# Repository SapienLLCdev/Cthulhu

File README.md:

## Cthulhu_Shield_Arduino

This is a library for using the Cthulhu Shield sensory substitution/augmentation development kit created by [Sapien LLC](http://sapienllc.com/). 

If you like what you see here, you can purchase a Cthulhu Shield [here!](https://sapienllc.com/shop/)

The Cthulhu Shield is an open-source Arduino Uno and Arduino Mega compatible sensory substitution/sensory augmentation device. It uses an 18 electrode grid to tactiley display signals on the tongue. The electrodes on the array can be activated with patterns of electrical pulses to depolarize nerve membranes in the tongue to create different types of touch sensations. You can use these touch sensations to draw shapes or simple images on the tongue, feel different sound frequencies, or receive turn by turn directions with your tongue.

Additionally, the Cthulhu Shield can sense whether or not your tongue is in contact with different electrodes using capacitive sensing. You can use the Cthulhu Shield to send keystrokes to your computer, control the cursor, or even control a mobility device. 

In this repository, we have provided a number of example projects to get you started with your Cthulhu, but we encourage you to experiment and build your own senses!

There are some awesome uses of sensory substitution already out there. For more information on these uses, or sensory substitution or augmentation in general, take a look at the links below. 
* [Brainport](https://www.youtube.com/watch?v=OKd56D2mvN0)
* [Wikipedia](https://en.wikipedia.org/wiki/Sensory_substitution)
* [Hear with your tongue](https://source.colostate.edu/words-mouth-csu-device-lets-hear-tongue/)
* [TedTalk](https://www.ted.com/talks/david_eagleman_can_we_create_new_senses_for_humans?language=en)

# Repository Contents:

* [Bare Minimum](https://github.com/SapienLLCdev/Cthulhu/tree/master/examples/BareMinimum)
* [Serial Input](https://github.com/SapienLLCdev/Cthulhu/tree/master/examples/SerialInput)
* [Accelerometer Example](https://github.com/SapienLLCdev/Cthulhu/tree/master/examples/accelerometer_Cthulhu_example)
* [GPS Directions](https://github.com/SapienLLCdev/Cthulhu/tree/master/examples/directions_example)
* [Make Patterns](https://github.com/SapienLLCdev/Cthulhu/tree/master/examples/make_patterns)
* [Thermal Camera](https://github.com/SapienLLCdev/Cthulhu/tree/master/examples/mega_heat_cam_with_shield)
* [Tactile Button](https://github.com/SapienLLCdev/Cthulhu/tree/master/examples/tactile_button_example)
* [Tactile Cursor](https://github.com/SapienLLCdev/Cthulhu/tree/master/examples/tactile_cursor)
* [Leonardo Tactile Cursor](https://github.com/SapienLLCdev/Cthulhu/tree/master/examples/Leonardo_tactile_cursor)
* [Tactile Keypad](https://github.com/SapienLLCdev/Cthulhu/tree/master/examples/tactile_keypad)
* [Cthulhu Camera Demo](https://github.com/SapienLLCdev/Cthulhu/tree/master/Android%20Examples/CthulhuCameraDemo)

# Cthulhu Shield Schematic:

.

# How to Use the Cthulhu Shield:

**Power:**
The Cthulhu Shield is made to be powered by plugging it directly into an Arduino Uno or Mega, and connecting the arduino to a USB cable attached to a properly grounded computer, or a smartphone or external battery pack. Users should not power their Arduino/Cthulhu Shield system with an AC wall adaptor, as a small number of these adaptors are not properly grounded or are otherwise unsafe and can cause injury or death if used with any electronic device.

**Input:**
When used with an Arduino Uno, the Cthulhu Shield can receive information directly from the USB port connected to a computer or smartphone, or via broken out Serial pins (RX, TX) which can used to communicate with other Arduinos/microcontrollers, or embedded devices such as Bluetooth modules or sensors with serial outputs. With an Arduino Mega, the extra IO pins can be leveraged to receive Digital or Analog signals that can be used to change the tactile output of the Cthulhu Shield. 

**Output:**
When used with an Arduino Uno, the Cthulhu Shield can send information directly via USB port connected to a computer or smarptphone, or via broken out Serial pins (RX, TX) which can used to communicate with other Arduinos/microcontrollers, or embedded devices such as Bluetooth modules or sensors with serial outputs. With an Arduino Mega, the extra IO pins can be leveraged to send Digital or Analog signals to external devices. 

**Electrode Control:**
Different types of sensations can be created on different electrodes and tongue locations by changing the pattern of pulses generated on each electrode. This can be done with the Cthulhu.UpdateStimuli() function. A user changes values in six (6), eighteen (18) element arrays. The values in these arrays correspond to whether one of the 18 electrodes is on or off, and what type of pulse, and pattern of pulses, is created on each electrode. Changing these patterns changes the type and quality of the sensation perceived by the user. This library was adapted from [work by Kurt Kaczmarek](https://www.sciencedirect.com/science/article/pii/S1026309811001702) and altered for the needs of our early research at Sapien LLC.

**Tongue Position Sensing:**
During electrotactile stimulation with the Cthulhu Shield, the Arduino can quickly sense the electrical potential on a given electrode, which changes if the tongue is in contact with the electrode or not. Placing your tongue on certain electrodes but not others, or swiping your tongue across different electrodes, can be detected by the Arduino, which can then send serial information (or with minor hacking, keystrokes and HID signals) to a computer or smartphone via the USB port, or external Bluetooth modules. 

Currently, tongue-position-sensing is supported only on ADC enabled Arduino pins (A0-A5 on the Uno and Mega). Position sensing on digital only pins should be possible and may be implemented in the near future. 

# How to Use this Repository:

If you are new to Github, Sparkfun has created an [excellent Github tutorial](https://learn.sparkfun.com/tutorials/using-github/all). If you want to get up and running quickly, just take a look at the [Download ZIP](https://learn.sparkfun.com/tutorials/using-github/all#download-zip) section.

Similarly, if you are new to Arduino, Sparkfun once again has a great [guide to installing Arduino Libraries](https://learn.sparkfun.com/tutorials/installing-an-arduino-library). After downloading the .ZIP file of the library you want from Github, follow the instructions above to integrate it with the Arduino IDE.

Please see the README files in the examples linked above for more information on their specific implementations!

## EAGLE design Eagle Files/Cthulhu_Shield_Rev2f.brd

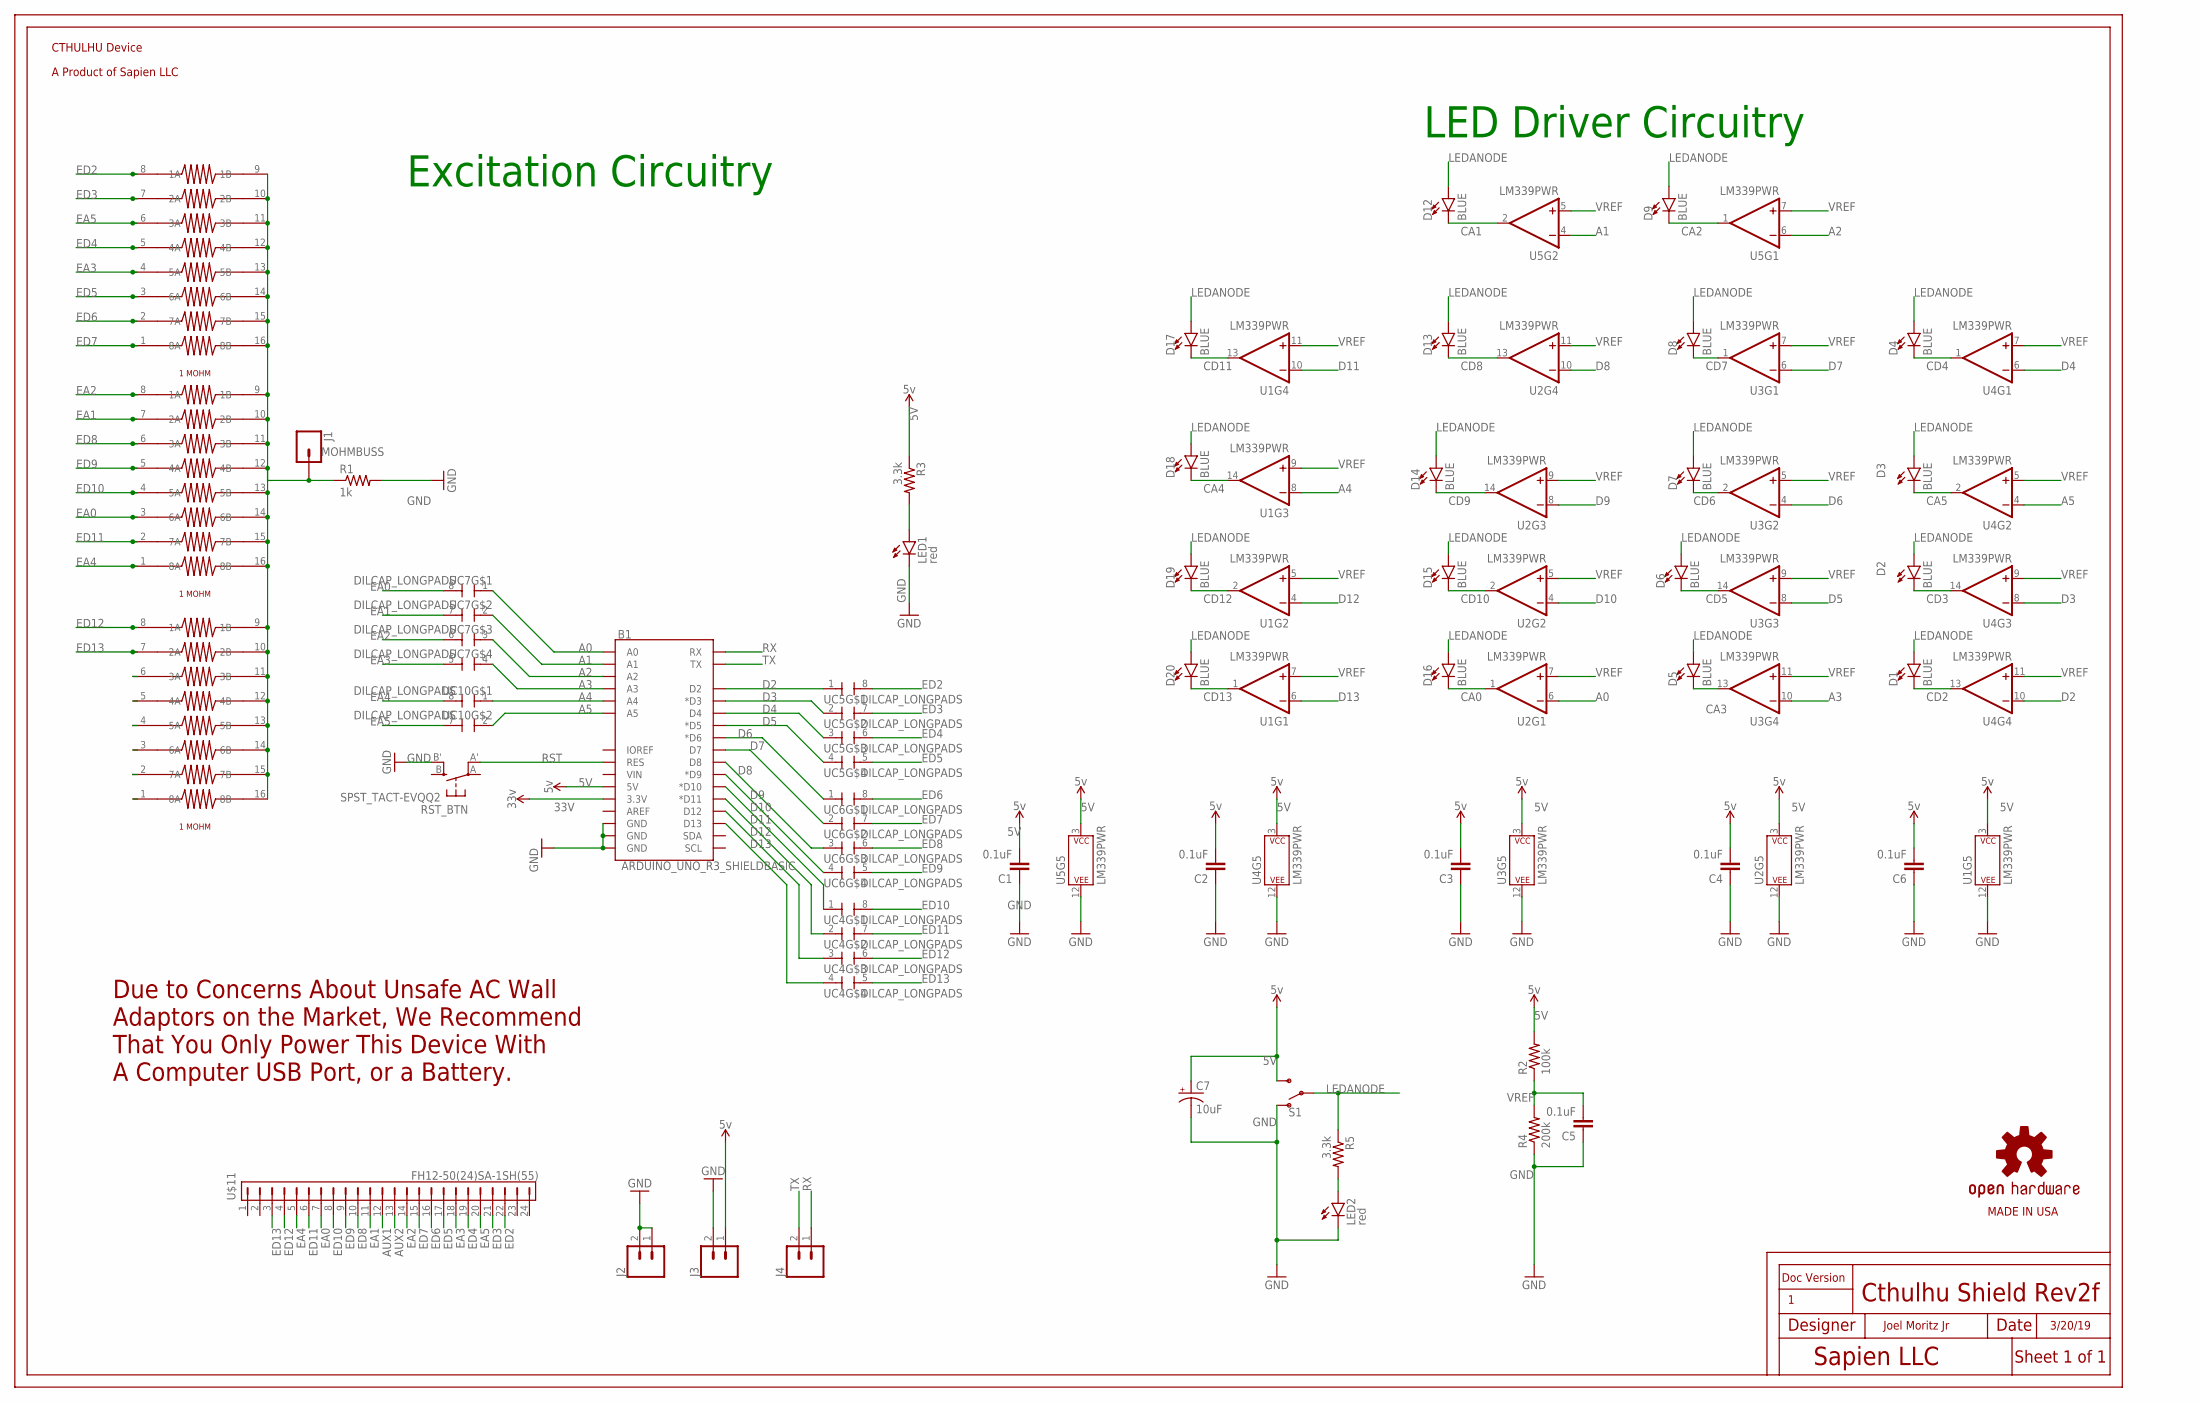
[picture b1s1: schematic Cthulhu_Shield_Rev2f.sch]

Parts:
B1: ARDUINO_UNO_R3_SHIELDBASIC; UNO_R3_SHIELD
C1, C2, C3, C4, C5, C6: 0.1uF; 0603
C7: 10uF; EIA3528
D1, D2, D3, D4, D5, D6, D7, D8, D9, D12, D13, D14, D15, D16, D17, D18, D19, D20: BLUE; LED-0603
J1: CONN_01; 1X01
J2, J3, J4: CONN_02; 1X02
LED1, LED2: red; LED-1206
LOGO1: OSHW-LOGOL; OSHW-LOGO-L
R1: 1k; 0402
R2: 100k; 0402
R3, R5: 3.3k; 0402
R4: 200k; 0402
RST_BTN: SPST_TACT-EVQQ2; EVQ-Q2
S1: SWITCH-SPDT-SMD-AYZ0202; SWITCH_DPDT_SMD_AYZ0202
U1, U2, U3, U4, U5: LM339PWR; TSSOP-14
U$1, U$2, U$3: 1MOHM8; JJ_CUSTOM_PARTS_1MOHMARRAY
U$4: NO_WALL_ADAPTOR
U$5: MADEINUSA
U$8: SAPEIN_LOGO_BOTTOM; SAPIEN_LOGO_BOTTOM
U$9: CTHULHU_LOGO; CTHULHU
U$11: FH12-50(24)SA-1SH(55); FH12-16S-1SH
UC4, UC5, UC6, UC7, UC10: DILCAP_LONGPADS; RESISTOR-DIL_4X0402ARV341_LONGPADS

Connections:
5V: B1.5V, C1.2, C2.2, C3.2, C4.2, C6.2, C7.A (+), J3.1, R2.2, R3.1, S1.3 (S), U1.3 (P$V+), U2.3 (P$V+), U3.3 (P$V+), U4.3 (P$V+), U5.3 (P$V+)
33V: B1.3.3V
A0: B1.A0, U2.6 (-IN), UC7.1
A1: B1.A1, U5.4 (-IN), UC7.2 (1)
A2: B1.A2, U5.6 (-IN), UC7.3 (1)
A3: B1.A3, U3.10 (-IN), UC7.4 (1)
A4: B1.A4, U1.8 (-IN), UC10.1
A5: B1.A5, U4.4 (-IN), UC10.2 (1)
AUX1: U$11.12
AUX2: U$11.13
CA0: D16.C, U2.1 (OUT)
CA1: D12.C, U5.2 (OUT)
CA2: D9.C, U5.1 (OUT)
CA3: D5.C, U3.13 (OUT)
CA4: D18.C, U1.14 (OUT)
CA5: D3.C, U4.2 (OUT)
CD2: D1.C, U4.13 (OUT)
CD3: D2.C, U4.14 (OUT)
CD4: D4.C, U4.1 (OUT)
CD5: D6.C, U3.14 (OUT)
CD6: D7.C, U3.2 (OUT)
CD7: D8.C, U3.1 (OUT)
CD8: D13.C, U2.13 (OUT)
CD9: D14.C, U2.14 (OUT)
CD10: D15.C, U2.2 (OUT)
CD11: D17.C, U1.13 (OUT)
CD12: D19.C, U1.2 (OUT)
CD13: D20.C, U1.1 (OUT)
D2: B1.D2, U4.10 (-IN), UC5.1
D3: B1.D3 (*D3), U4.8 (-IN), UC5.2 (1)
D4: B1.D4, U4.6 (-IN), UC5.3 (1)
D5: B1.D5 (*D5), U3.8 (-IN), UC5.4 (1)
D6: B1.D6 (*D6), U3.4 (-IN), UC6.1
D7: B1.D7, U3.6 (-IN), UC6.2 (1)
D8: B1.D8, U2.10 (-IN), UC6.3 (1)
D9: B1.D9 (*D9), U2.8 (-IN), UC6.4 (1)
D10: B1.D10 (*D10), U2.4 (-IN), UC4.1
D11: B1.D11 (*D11), U1.10 (-IN), UC4.2 (1)
D12: B1.D12, U1.4 (-IN), UC4.3 (1)
D13: B1.D13, U1.6 (-IN), UC4.4 (1)
EA0: U$2.3 (6A), U$11.7, UC7.8 (2)
EA1: U$2.7 (2A), U$11.11, UC7.7 (2)
EA2: U$2.8 (1A), U$11.14, UC7.6 (2)
EA3: U$1.4 (5A), U$11.18, UC7.5 (2)
EA4: U$2.1 (8A), U$11.5, UC10.8 (2)
EA5: U$1.6 (3A), U$11.20, UC10.7 (2)
ED2: U$1.8 (1A), U$11.22, UC5.8 (2)
ED3: U$1.7 (2A), U$11.21, UC5.7 (2)
ED4: U$1.5 (4A), U$11.19, UC5.6 (2)
ED5: U$1.3 (6A), U$11.17, UC5.5 (2)
ED6: U$1.2 (7A), U$11.16, UC6.8 (2)
ED7: U$1.1 (8A), U$11.15, UC6.7 (2)
ED8: U$2.6 (3A), U$11.10, UC6.6 (2)
ED9: U$2.5 (4A), U$11.9, UC6.5 (2)
ED10: U$2.4 (5A), U$11.8, UC4.8 (2)
ED11: U$2.2 (7A), U$11.6, UC4.7 (2)
ED12: U$3.8 (1A), U$11.4, UC4.6 (2)
ED13: U$3.7 (2A), U$11.3, UC4.5 (2)
GND: B1.GND@0 (GND), B1.GND@1 (GND), B1.GND@2 (GND), C1.1, C2.1, C3.1, C4.1, C5.1, C6.1, C7.C (-), J2.1, J2.2, J3.2, LED1.C, LED2.C, R1.2, R4.1, RST_BTN.B' (S1), S1.1 (O), U1.12 (P$V-), U2.12 (P$V-), U3.12 (P$V-), U4.12 (P$V-), U5.12 (P$V-)
LEDANODE: D1.A, D2.A, D3.A, D4.A, D5.A, D6.A, D7.A, D8.A, D9.A, D12.A, D13.A, D14.A, D15.A, D16.A, D17.A, D18.A, D19.A, D20.A, R5.1, S1.2
MOHMBUSS: J1.1, R1.1, U$1.9 (1B), U$1.10 (2B), U$1.11 (3B), U$1.12 (4B), U$1.13 (5B), U$1.14 (6B), U$1.15 (7B), U$1.16 (8B), U$2.9 (1B), U$2.10 (2B), U$2.11 (3B), U$2.12 (4B), U$2.13 (5B), U$2.14 (6B), U$2.15 (7B), U$2.16 (8B), U$3.9 (1B), U$3.10 (2B), U$3.11 (3B), U$3.12 (4B), U$3.13 (5B), U$3.14 (6B), U$3.15 (7B), U$3.16 (8B)
unnamed: LED1.A, R3.2
unnamed: LED2.A, R5.2
RST: B1.RES, RST_BTN.A' (P1)
RX: B1.RX, J4.1
TX: B1.TX, J4.2
VREF: C5.2, R2.1, R4.2, U1.5 (+IN), U1.7 (+IN), U1.9 (+IN), U1.11 (+IN), U2.5 (+IN), U2.7 (+IN), U2.9 (+IN), U2.11 (+IN), U3.5 (+IN), U3.7 (+IN), U3.9 (+IN), U3.11 (+IN), U4.5 (+IN), U4.7 (+IN), U4.9 (+IN), U4.11 (+IN), U5.5 (+IN), U5.7 (+IN)

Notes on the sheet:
Doc Version
Designer
Date
Sheet 1 of 1
Cthulhu Shield Rev2f
Joel Moritz Jr
3/20/19
Sapien LLC
LED Driver Circuitry
Excitation Circuitry

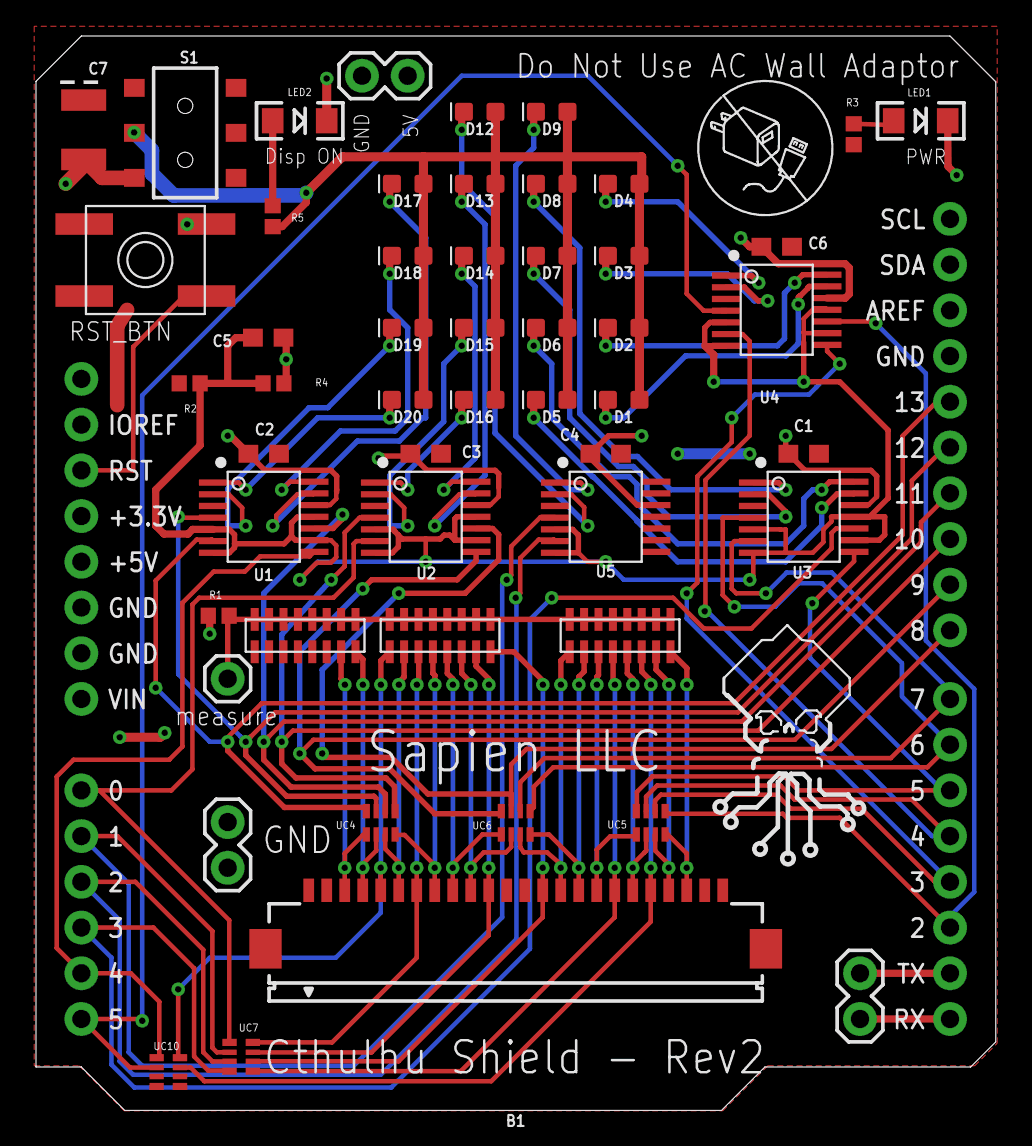
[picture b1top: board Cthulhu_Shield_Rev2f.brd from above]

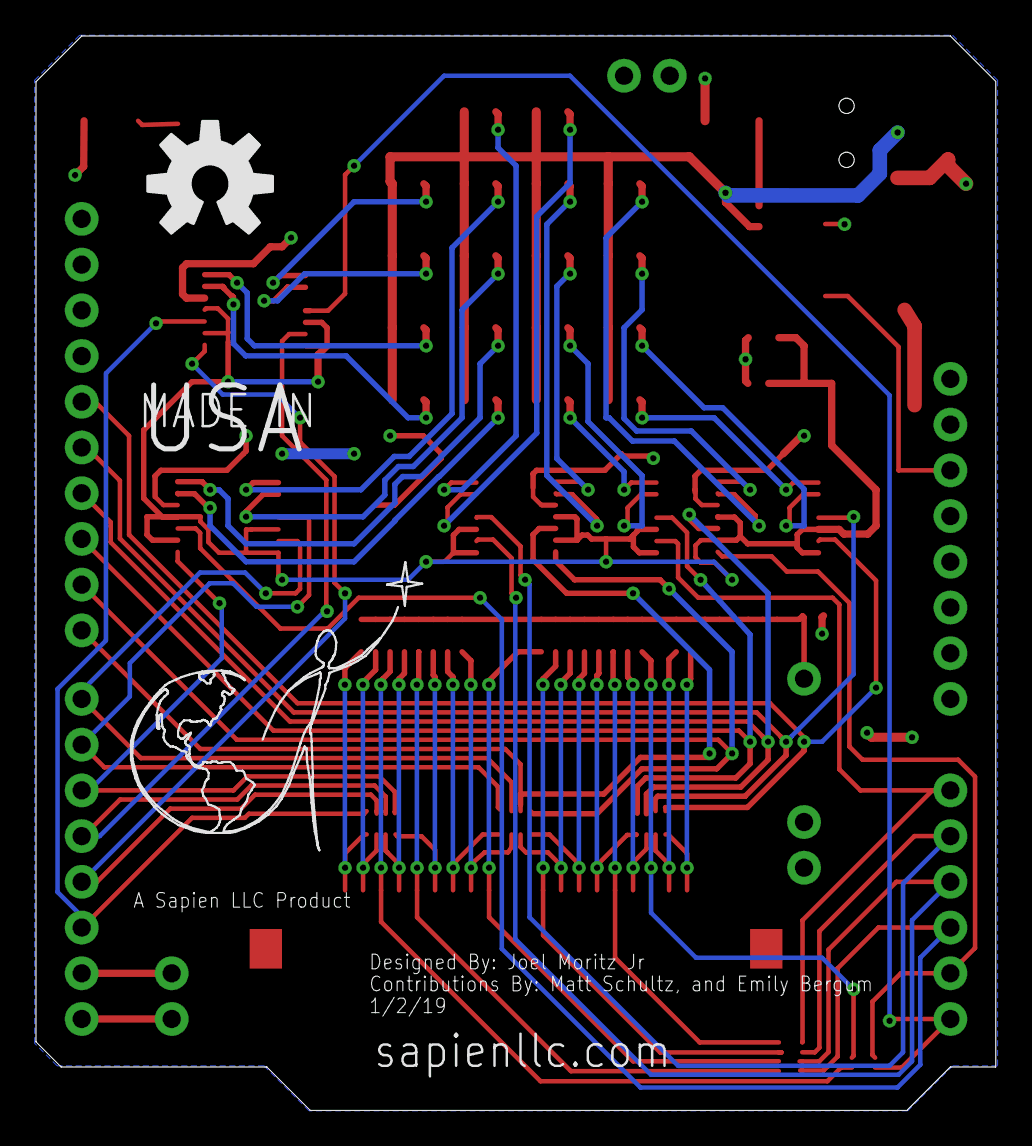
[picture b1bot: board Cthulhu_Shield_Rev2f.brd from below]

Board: 2 copper layers, 53.3 x 59.7 mm, 58 parts (2 on the bottom side), 64 nets.

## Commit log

2019-01-30 coppermaa credit
2019-01-30 image test
2019-01-30 for jj
2019-01-30 for jj 2
2019-01-30 Schematic added
2019-01-30 cthulhu shield schematic added
2019-01-30 pdf -> jpg schematic
2019-01-30 Schematic jpg
2019-01-30 Create README.md
    README for tactile button example added
2019-01-30 readme placeholder
2019-01-30 Create README.md
    README added for check waveform test function
2019-01-30 How to use this repository
2019-01-30 Demonstration_example serial output added. README added.
    Demonstration example modified to include serial output.
    README added for demonstration example.
2019-01-30 How to Use the Cthulhu Shield
2019-01-30 readability and link to kickstarter
2019-01-30 broken links
2019-01-30 period
2019-02-08 pp[16] -> pp[18]
2019-02-08 slight wording change
2019-02-08 Additional Description and links added.
2019-02-08 typo fix
2019-02-08 Edited new material
    smol edits
2019-02-08 edits
2019-02-09 smol edit
2019-02-09 SMOL EDIT 2
2019-02-10 Example photo upload
    photos of needed hardware
2019-02-10 Readme draft
2019-02-10 smaller images for readme
2019-02-10 Firmware for Atmega16U2
    Wanted local copies in case coopermaa ever deletes his repo.
2019-02-10 Flip walk through images and driver update
2019-02-10 directions and update drivers troubleshooting.
2019-02-10 new image
2019-02-12 minor edit
2019-02-13 Cleanup
    Put jpg's into one folder, removed the pdf and docx directions
2019-02-13 put firmware in folder
2019-02-13 gif and images added
2019-02-13 Tacctile curosr documented
2019-02-14 More jpgs added
    Added infraredsmall and infrared_setup
2019-02-14 more jpgs
    added more jpgs and moved some from tactile_curser
2019-02-14 more jpgs
2019-02-14 jpgs
2019-02-15 removed serial input in the loop
2019-02-15 seperated demo and serial, added bareminimum
2019-02-15 table of contents examples
2019-02-15 consolidate images in main jpg folder
2019-02-15 readme edits for jpgs
2019-02-15 more jpgs for Serial Input
2019-02-15 cool term jpgs
2019-02-15 BareMinimum pdfs
2019-02-17 wording
2019-02-17 grammar
2019-02-18 Mac Accessibility JPEGs
2019-02-18 mac setup 1
2019-02-18 Updating Tactile Key/button/cursor examples
    included intensity control
2019-02-22 accelerometer_Cthulhu_example
    Arduino code, README, and jpgs
2019-03-05 Filled in README for Android Examples folder
2019-03-05 Tactile Waves Cthulhu Demo
    Added source code for the Tactile Waves Cthulhu Demo
2019-03-05 Filled in README
    Filled in README file with basic description and installation instructions
2019-03-05 Edit README
    added missing parentheses
2019-03-05 Created README
    Created a README file for the Tactile Waves Cthulhu Demo
2019-03-05 fixed typo
    Fixed a typo
2019-03-05 mini_photocell_example with README and jpgs
2019-03-07 force_sensitve_resistor_example
    arduino code, README, and jpgs
2019-05-11 Create Supporters.md
    A thank you to the backers who supported us at the 'support research and development' level on our Kickstarter Campaign.
2019-05-11 formatting
2019-05-11 added app links
2019-05-11 update links
2019-05-11 Leonardo Mouse Code
    Code to use a Cthulhu Shield and arduino Leonardo as a full function computer mouse. Includes right click, and click drag functions, no hardware hacks, or computer settings need to be changed. Direct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
2019-05-11 added Leonardo tactile cursor
2019-05-11 resize image
2019-05-12 smaller images
2019-05-20 Updated infrared camera README
2019-05-23 Operations instructions for tongue mouse
2019-05-23 links to video and instructions
2019-06-08 scroll updates
    Scrolling, two-speed control, more stable right click.
2019-06-08 adjusted speed of scroll
2019-06-09 Cut speed on slow mode by 50%
    Settings, and configurations that I like.
2019-06-12 A more stable mouse with different modes
    Code is messy, but has increased functionality.
2019-07-15 Use weak pullups and volt decay time to sense tongue contact
    Uses the weak internal pullups in atmega chip to lightly pulse the pins/electodes, then measures the time it takes for the voltage on pins/electrodes to decay to logic level low.
2019-07-16 Heat cam updated
2019-09-03 addition of drafts to remove time/period limitations
2019-09-04 Changed_array_for_horz_mouthpiece
2019-11-02 serial print functions included
2019-12-10 Prelim Braccio Controller
2019-12-19 Under development, but functional
2019-12-20 Eagle files added
2020-01-22 change purchase link to sparkfun
2020-07-19 Update Cthulhu.cpp
    Int function should have return statement. I was getting undefined behaviour causing the for loop to not terminate due to this.
2020-08-26 Updated shopping link to Sapien website
2021-08-01 Changes to be committed: new file: CthulhuSqueezenetDemo/README.md new file: CthulhuSqueezenetDemo/SerialInput.ino new file: CthulhuSqueezenetDemo/app/build.gradle new file: CthulhuSqueezenetDemo/app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
2021-08-01 Create LICENSE

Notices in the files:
parts and their libraries:
SparkFun-Boards: Licensing: Creative Commons ShareAlike 4.0 International - https://creativecommons.org/licenses/by-sa/4.0
